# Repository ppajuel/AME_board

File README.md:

# AME_board
AME_board (Aquila Mobile Expansio board) is a low cost expansion board for IGEP COM AQUILA. This board allows to use [IGEP COM AQUILA AM335x](https://isee.biz/products/igep-processor-boards/igep-com-aquila-am335x) as a battery powered M2M device. Its features are:

* Lipo Bat handler and 5V step-UP
* Modem GPRS with ANT conn
* Serial debug 3v3
* Jumper boot
* RTC BAT
* Switch POWERKILL
* PCB frendly and soldable
* MicroUSB power
* Optional: debug all SODIMM
* Bat connector and Header

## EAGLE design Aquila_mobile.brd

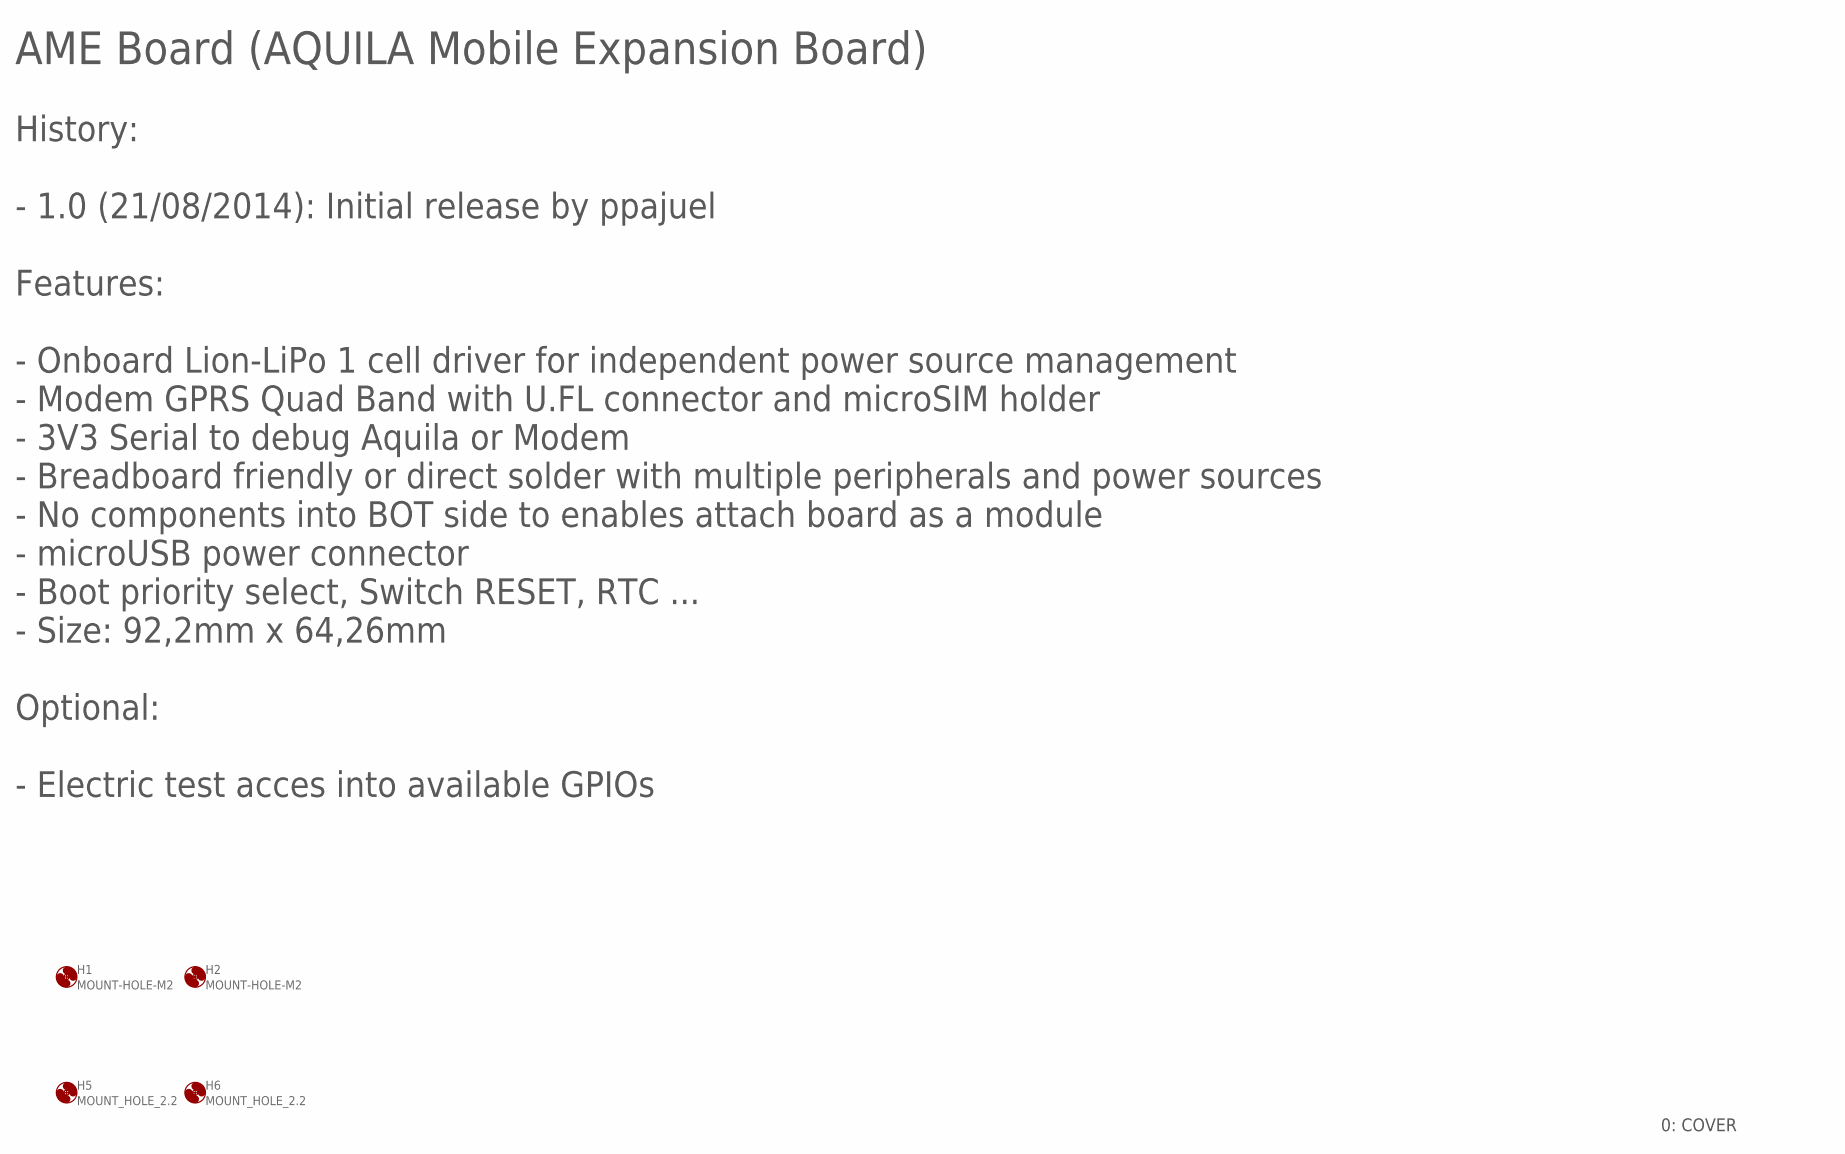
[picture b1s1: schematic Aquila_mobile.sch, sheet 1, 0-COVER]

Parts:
H1, H2: MOUNT-HOLE-M2; 5,0
H5, H6: MOUNT_HOLE_2.2; HOLE-2.2

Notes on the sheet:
History: - 1.0 (21/08/2014): Initial release by ppajuel Features: - Onboard Lion-LiPo 1 cell driver for independent power source management - Modem GPRS Quad Band with U.FL connector and microSIM holder - 3V3 Serial to debug Aquila or Modem - Breadboard friendly or direct solder with multiple perip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
AME Board (AQUILA Mobile Expansion Board)
0: COVER

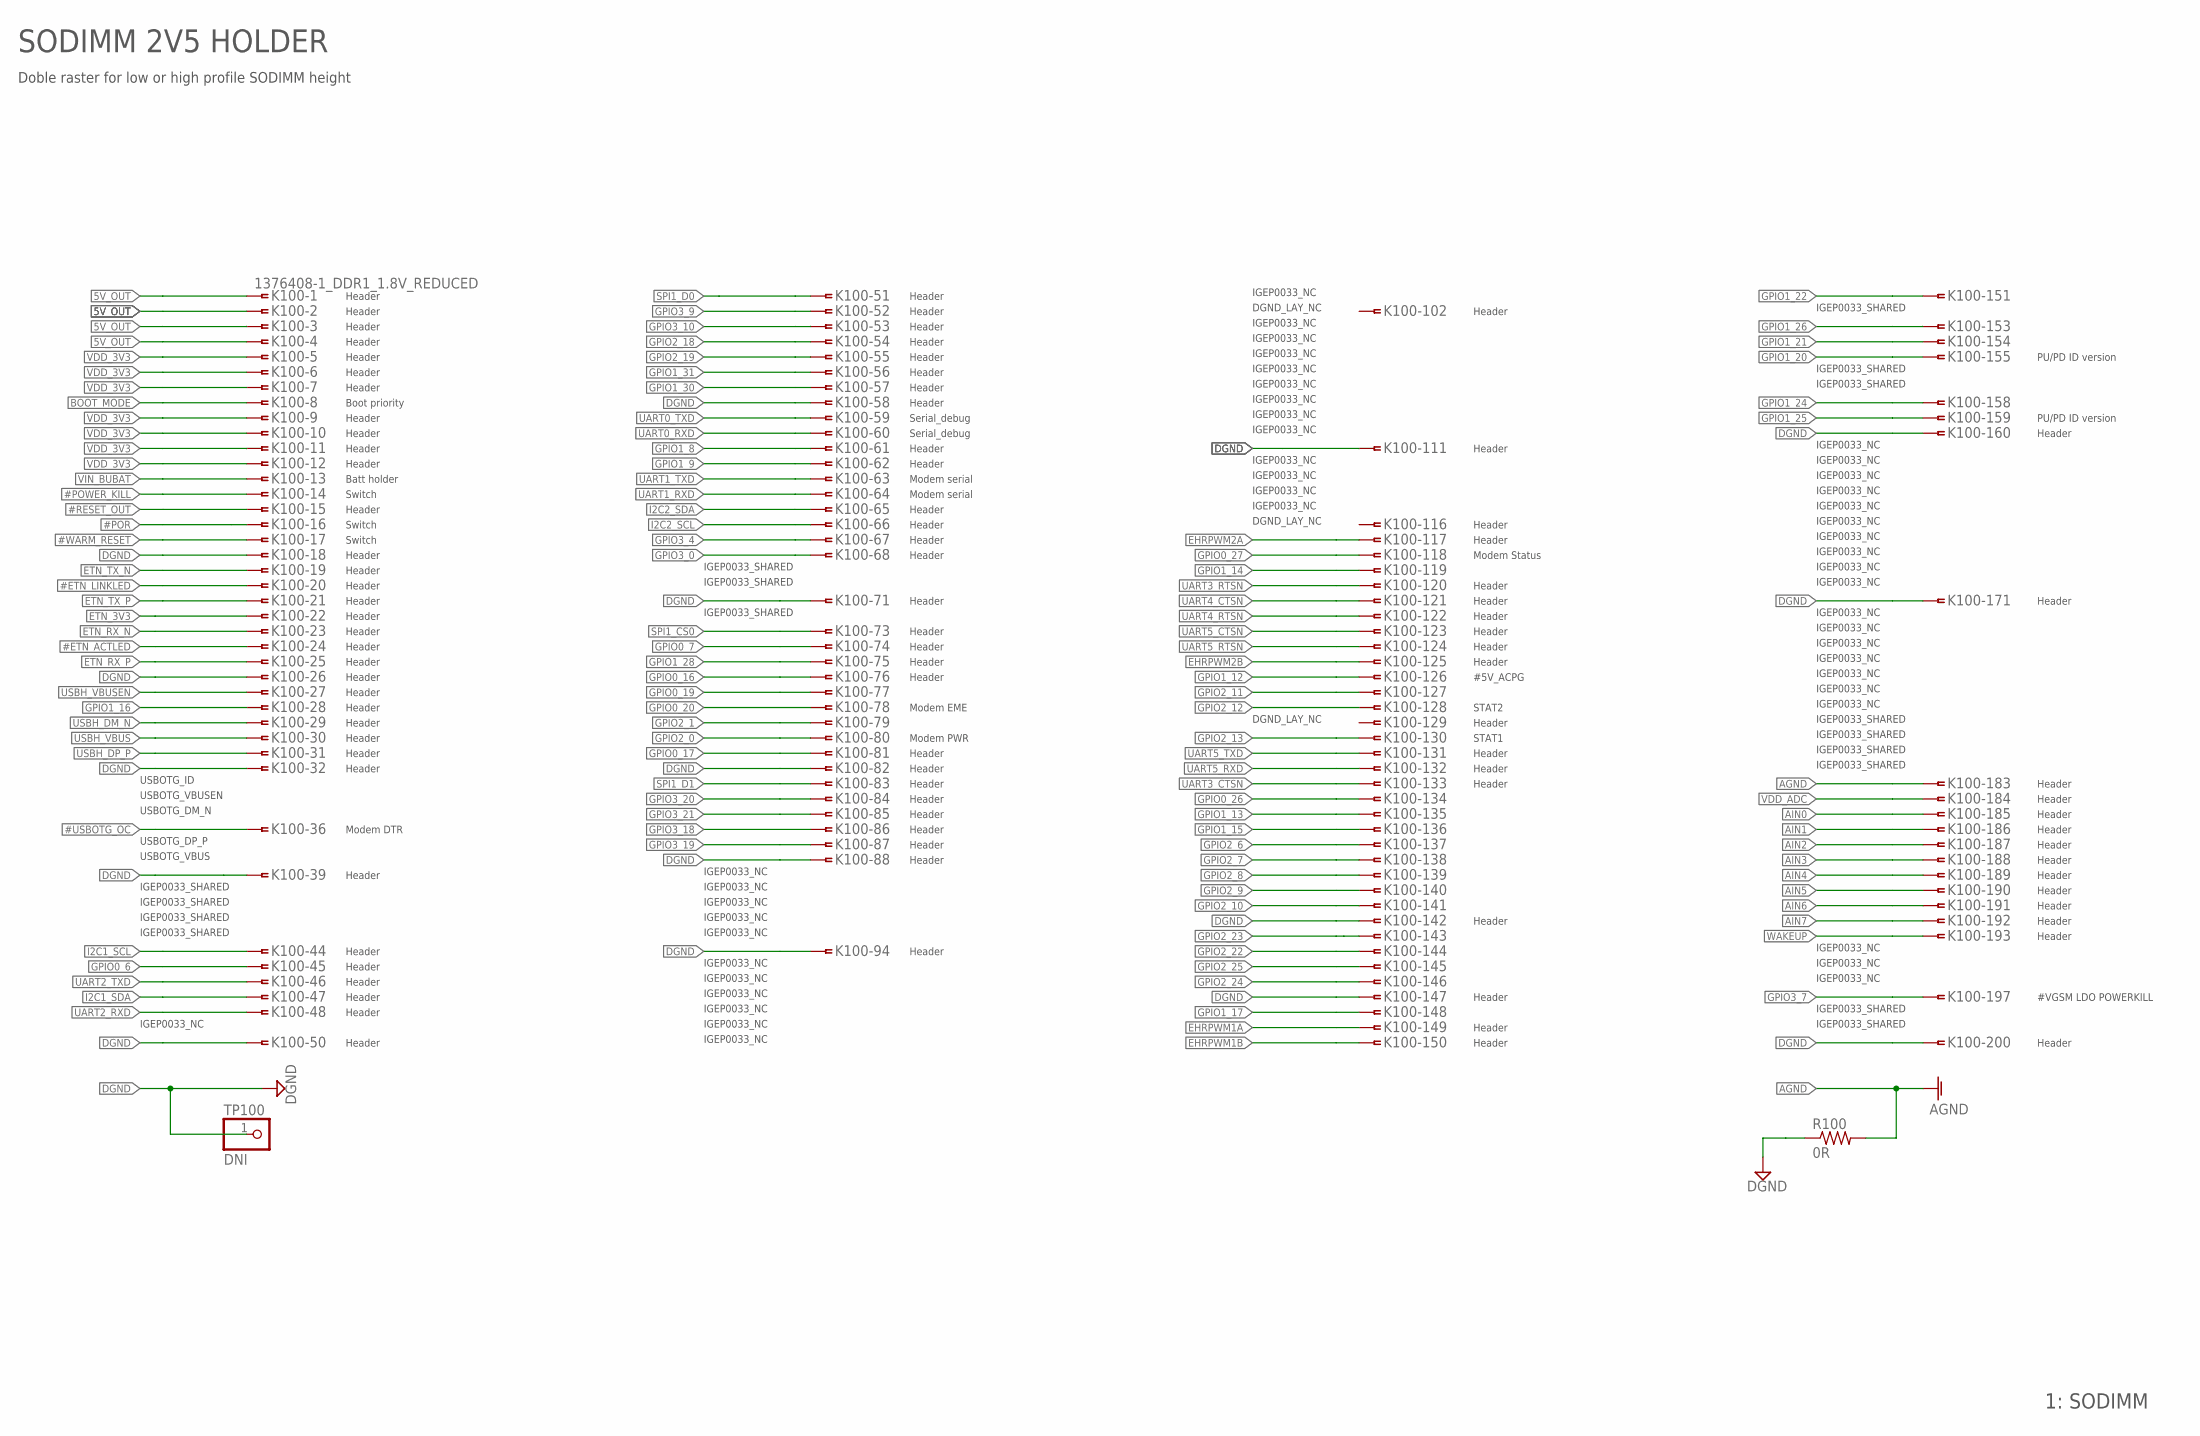
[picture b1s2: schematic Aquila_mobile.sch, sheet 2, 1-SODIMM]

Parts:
K100: 1376408-1_DDR1_1.8V_REDUCED; 1-1376408-1_REDUCED
R100: 0R; R0402
TP100: DNI; 1X01

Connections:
5V_OUT: K100.1, K100.2, K100.3, K100.4; also elsewhere on the board
#ETN_ACTLED: K100.24; also elsewhere on the board
#ETN_LINKLED: K100.20; also elsewhere on the board
#POR: K100.16; also elsewhere on the board
#POWER_KILL: K100.14; also elsewhere on the board
#RESET_OUT: K100.15; also elsewhere on the board
#USBOTG_OC: K100.36; also elsewhere on the board
#WARM_RESET: K100.17; also elsewhere on the board
AGND: K100.183, R100.2; also elsewhere on the board
AIN0: K100.185; also elsewhere on the board
AIN1: K100.186; also elsewhere on the board
AIN2: K100.187; also elsewhere on the board
AIN3: K100.188; also elsewhere on the board
AIN4: K100.189; also elsewhere on the board
AIN5: K100.190; also elsewhere on the board
AIN6: K100.191; also elsewhere on the board
AIN7: K100.192; also elsewhere on the board
BOOT_MODE: K100.8; also elsewhere on the board
DGND: K100.18, K100.26, K100.32, K100.39, K100.50, K100.58, K100.71, K100.82, K100.88, K100.94, K100.111, K100.142, K100.147, K100.160, K100.171, K100.200, R100.1, TP100.1; also elsewhere on the board
EHRPWM1A: K100.149; also elsewhere on the board
EHRPWM1B: K100.150; also elsewhere on the board
EHRPWM2A: K100.117; also elsewhere on the board
EHRPWM2B: K100.125; also elsewhere on the board
ETN_3V3: K100.22; also elsewhere on the board
ETN_RX_N: K100.23; also elsewhere on the board
ETN_RX_P: K100.25; also elsewhere on the board
ETN_TX_N: K100.19; also elsewhere on the board
ETN_TX_P: K100.21; also elsewhere on the board
GPIO0_6: K100.45; also elsewhere on the board
GPIO0_7: K100.74; also elsewhere on the board
GPIO0_16: K100.76; also elsewhere on the board
GPIO0_17: K100.81; also elsewhere on the board
GPIO0_19: K100.77; also elsewhere on the board
GPIO0_20: K100.78; also elsewhere on the board
GPIO0_26: K100.134; also elsewhere on the board
GPIO0_27: K100.118; also elsewhere on the board
GPIO1_8: K100.61; also elsewhere on the board
GPIO1_9: K100.62; also elsewhere on the board
GPIO1_12: K100.126; also elsewhere on the board
GPIO1_13: K100.135; also elsewhere on the board
GPIO1_14: K100.119; also elsewhere on the board
GPIO1_15: K100.136; also elsewhere on the board
GPIO1_16: K100.28; also elsewhere on the board
GPIO1_17: K100.148; also elsewhere on the board
GPIO1_20: K100.155; also elsewhere on the board
GPIO1_21: K100.154; also elsewhere on the board
GPIO1_22: K100.151; also elsewhere on the board
GPIO1_24: K100.158; also elsewhere on the board
GPIO1_25: K100.159; also elsewhere on the board
GPIO1_26: K100.153; also elsewhere on the board
GPIO1_28: K100.75; also elsewhere on the board
GPIO1_30: K100.57; also elsewhere on the board
GPIO1_31: K100.56; also elsewhere on the board
GPIO2_0: K100.80; also elsewhere on the board
GPIO2_1: K100.79; also elsewhere on the board
GPIO2_6: K100.137; also elsewhere on the board
GPIO2_7: K100.138; also elsewhere on the board
GPIO2_8: K100.139; also elsewhere on the board
GPIO2_9: K100.140; also elsewhere on the board
GPIO2_10: K100.141; also elsewhere on the board
GPIO2_11: K100.127; also elsewhere on the board
GPIO2_12: K100.128; also elsewhere on the board
GPIO2_13: K100.130; also elsewhere on the board
GPIO2_18: K100.54; also elsewhere on the board
GPIO2_19: K100.55; also elsewhere on the board
GPIO2_22: K100.144; also elsewhere on the board
GPIO2_23: K100.143; also elsewhere on the board
GPIO2_24: K100.146; also elsewhere on the board
GPIO2_25: K100.145; also elsewhere on the board
GPIO3_0: K100.68; also elsewhere on the board
GPIO3_4: K100.67; also elsewhere on the board
GPIO3_7: K100.197; also elsewhere on the board
GPIO3_9: K100.52; also elsewhere on the board
GPIO3_10: K100.53; also elsewhere on the board
GPIO3_18: K100.86; also elsewhere on the board
GPIO3_19: K100.87; also elsewhere on the board
GPIO3_20: K100.84; also elsewhere on the board
GPIO3_21: K100.85; also elsewhere on the board
I2C1_SCL: K100.44; also elsewhere on the board
I2C1_SDA: K100.47; also elsewhere on the board
I2C2_SCL: K100.66; also elsewhere on the board
I2C2_SDA: K100.65; also elsewhere on the board
SPI1_CS0: K100.73; also elsewhere on the board
SPI1_D0: K100.51; also elsewhere on the board
SPI1_D1: K100.83; also elsewhere on the board
UART0_RXD: K100.60; also elsewhere on the board
UART0_TXD: K100.59; also elsewhere on the board
UART1_RXD: K100.64; also elsewhere on the board
UART1_TXD: K100.63; also elsewhere on the board
UART2_RXD: K100.48; also elsewhere on the board
UART2_TXD: K100.46; also elsewhere on the board
UART3_CTSN: K100.133; also elsewhere on the board
UART3_RTSN: K100.120; also elsewhere on the board
UART4_CTSN: K100.121; also elsewhere on the board
UART4_RTSN: K100.122; also elsewhere on the board
UART5_CTSN: K100.123; also elsewhere on the board
UART5_RTSN: K100.124; also elsewhere on the board
UART5_RXD: K100.132; also elsewhere on the board
UART5_TXD: K100.131; also elsewhere on the board
USBH_DM_N: K100.29; also elsewhere on the board
USBH_DP_P: K100.31; also elsewhere on the board
USBH_VBUS: K100.30; also elsewhere on the board
USBH_VBUSEN: K100.27; also elsewhere on the board
VDD_3V3: K100.5, K100.6, K100.7, K100.9, K100.10, K100.11, K100.12; also elsewhere on the board
VDD_ADC: K100.184; also elsewhere on the board
VIN_BUBAT: K100.13; also elsewhere on the board
WAKEUP: K100.193; also elsewhere on the board

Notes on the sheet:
SODIMM 2V5 HOLDER
USBOTG_ID
USBOTG_VBUSEN
USBOTG_DM_N
USBOTG_DP_P
USBOTG_VBUS
IGEP0033_SHARED
IGEP0033_NC
Serial_debug
Switch
Boot priority
Modem serial
Modem EME
#VGSM LDO POWERKILL
#5V_ACPG
STAT1
STAT2
1: SODIMM
Doble raster for low or high profile SODIMM height
Batt holder
Modem DTR
Modem PWR
Header
PU/PD ID version
Modem Status
DGND_LAY_NC

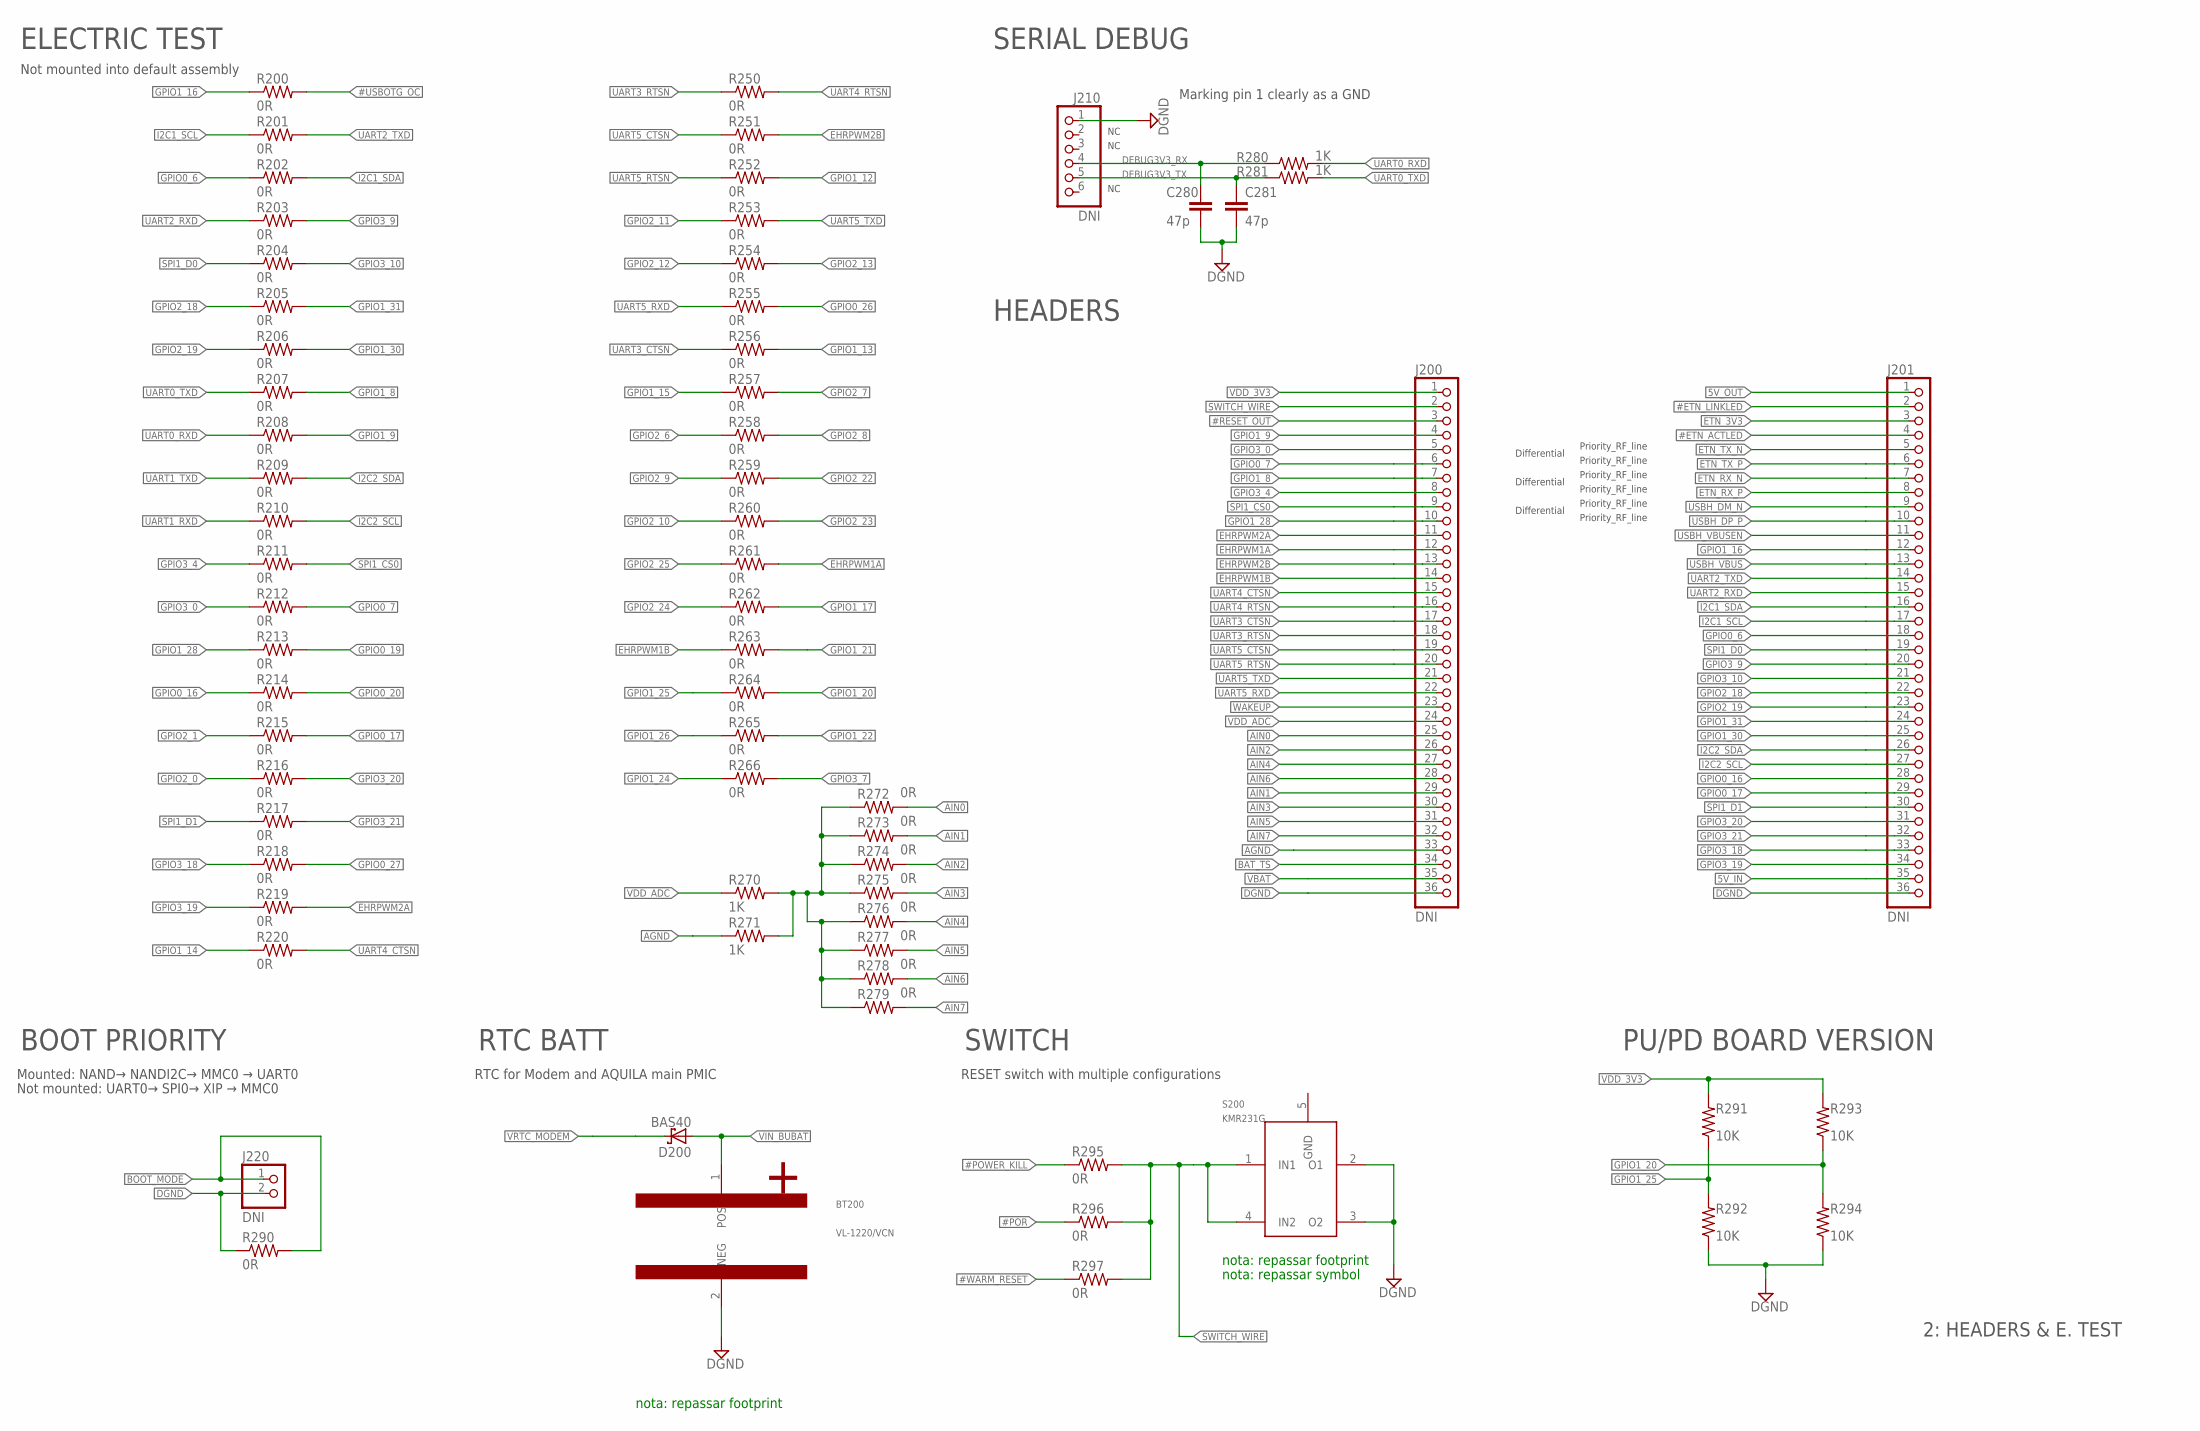
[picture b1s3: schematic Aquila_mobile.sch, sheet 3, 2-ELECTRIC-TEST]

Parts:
BT200: VL-1220/VCN
C280, C281: 47p; C0603
D200: BAS40; SOT23
J200, J201: DNI; 1X36
J210: DNI; 1X06
J220: DNI; 1X02
R200, R201, R202, R203, R204, R205, R206, R207, R208, R209, R210, R211, R212, R213, R214, R215, R216, R217, R218, R219, R220, R250, R251, R252, R253, R254, R255, R256, R257, R258, R259, R260, R262, R263, R264, R265, R266, R272, R273, R274, R275, R276, R277, R278, R279, R295, R296, R297: 0R; R0201
R261, R290: 0R; R0402
R270, R271: 1K; R0402
R280, R281: 1K; R0603
R291, R292, R293, R294: 10K; R0402
S200: KMR231G

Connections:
5V_IN: J201.35; also elsewhere on the board
5V_OUT: J201.1; also elsewhere on the board
#ETN_ACTLED: J201.4; also elsewhere on the board
#ETN_LINKLED: J201.2; also elsewhere on the board
#POR: R296.1; also elsewhere on the board
#POWER_KILL: R295.1; also elsewhere on the board
#RESET_OUT: J200.3; also elsewhere on the board
#USBOTG_OC: R200.2; also elsewhere on the board
#WARM_RESET: R297.1; also elsewhere on the board
ADCREFERENCE: R270.2, R271.2, R272.1, R273.1, R274.1, R275.1, R276.1, R277.1, R278.1, R279.1
AGND: J200.33, R271.1; also elsewhere on the board
AIN0: J200.25, R272.2; also elsewhere on the board
AIN1: J200.29, R273.2; also elsewhere on the board
AIN2: J200.26, R274.2; also elsewhere on the board
AIN3: J200.30, R275.2; also elsewhere on the board
AIN4: J200.27, R276.2; also elsewhere on the board
AIN5: J200.31, R277.2; also elsewhere on the board
AIN6: J200.28, R278.2; also elsewhere on the board
AIN7: J200.32, R279.2; also elsewhere on the board
BAT_TS: J200.34; also elsewhere on the board
BOOT_MODE: J220.1, R290.2; also elsewhere on the board
DEBUG3V3_RX: C280.1, J210.4, R280.1; also elsewhere on the board
DEBUG3V3_TX: C281.1, J210.5, R281.1; also elsewhere on the board
DGND: BT200.2 (NEG), C280.2, C281.2, J200.36, J201.36, J210.1, J220.2, R290.1, R292.1, R294.1, S200.2 (O1), S200.3 (O2); also elsewhere on the board
EHRPWM1A: J200.12, R261.2; also elsewhere on the board
EHRPWM1B: J200.14, R263.1; also elsewhere on the board
EHRPWM2A: J200.11, R219.2; also elsewhere on the board
EHRPWM2B: J200.13, R251.2; also elsewhere on the board
ETN_3V3: J201.3; also elsewhere on the board
ETN_RX_N: J201.7; also elsewhere on the board
ETN_RX_P: J201.8; also elsewhere on the board
ETN_TX_N: J201.5; also elsewhere on the board
ETN_TX_P: J201.6; also elsewhere on the board
GPIO0_6: J201.18, R202.1; also elsewhere on the board
GPIO0_7: J200.6, R212.2; also elsewhere on the board
GPIO0_16: J201.28, R214.1; also elsewhere on the board
GPIO0_17: J201.29, R215.2; also elsewhere on the board
GPIO0_19: R213.2; also elsewhere on the board
GPIO0_20: R214.2; also elsewhere on the board
GPIO0_26: R255.2; also elsewhere on the board
GPIO0_27: R218.2; also elsewhere on the board
GPIO1_8: J200.7, R207.2; also elsewhere on the board
GPIO1_9: J200.4, R208.2; also elsewhere on the board
GPIO1_12: R252.2; also elsewhere on the board
GPIO1_13: R256.2; also elsewhere on the board
GPIO1_14: R220.1; also elsewhere on the board
GPIO1_15: R257.1; also elsewhere on the board
GPIO1_16: J201.12, R200.1; also elsewhere on the board
GPIO1_17: R262.2; also elsewhere on the board
GPIO1_20: R264.2, R293.1, R294.2; also elsewhere on the board
GPIO1_21: R263.2; also elsewhere on the board
GPIO1_22: R265.2; also elsewhere on the board
GPIO1_24: R266.1; also elsewhere on the board
GPIO1_25: R264.1, R291.1, R292.2; also elsewhere on the board
GPIO1_26: R265.1; also elsewhere on the board
GPIO1_28: J200.10, R213.1; also elsewhere on the board
GPIO1_30: J201.25, R206.2; also elsewhere on the board
GPIO1_31: J201.24, R205.2; also elsewhere on the board
GPIO2_0: R216.1; also elsewhere on the board
GPIO2_1: R215.1; also elsewhere on the board
GPIO2_6: R258.1; also elsewhere on the board
GPIO2_7: R257.2; also elsewhere on the board
GPIO2_8: R258.2; also elsewhere on the board
GPIO2_9: R259.1; also elsewhere on the board
GPIO2_10: R260.1; also elsewhere on the board
GPIO2_11: R253.1; also elsewhere on the board
GPIO2_12: R254.1; also elsewhere on the board
GPIO2_13: R254.2; also elsewhere on the board
GPIO2_18: J201.22, R205.1; also elsewhere on the board
GPIO2_19: J201.23, R206.1; also elsewhere on the board
GPIO2_22: R259.2; also elsewhere on the board
GPIO2_23: R260.2; also elsewhere on the board
GPIO2_24: R262.1; also elsewhere on the board
GPIO2_25: R261.1; also elsewhere on the board
GPIO3_0: J200.5, R212.1; also elsewhere on the board
GPIO3_4: J200.8, R211.1; also elsewhere on the board
GPIO3_7: R266.2; also elsewhere on the board
GPIO3_9: J201.20, R203.2; also elsewhere on the board
GPIO3_10: J201.21, R204.2; also elsewhere on the board
GPIO3_18: J201.33, R218.1; also elsewhere on the board
GPIO3_19: J201.34, R219.1; also elsewhere on the board
GPIO3_20: J201.31, R216.2; also elsewhere on the board
GPIO3_21: J201.32, R217.2; also elsewhere on the board
I2C1_SCL: J201.17, R201.1; also elsewhere on the board
I2C1_SDA: J201.16, R202.2; also elsewhere on the board
I2C2_SCL: J201.27, R210.2; also elsewhere on the board
I2C2_SDA: J201.26, R209.2; also elsewhere on the board
SPI1_CS0: J200.9, R211.2; also elsewhere on the board
SPI1_D0: J201.19, R204.1; also elsewhere on the board
SPI1_D1: J201.30, R217.1; also elsewhere on the board
SWITCH_WIRE: J200.2, R295.2, R296.2, R297.2, S200.1 (IN1), S200.4 (IN2)
UART0_RXD: R208.1, R280.2; also elsewhere on the board
UART0_TXD: R207.1, R281.2; also elsewhere on the board
UART1_RXD: R210.1; also elsewhere on the board
UART1_TXD: R209.1; also elsewhere on the board
UART2_RXD: J201.15, R203.1; also elsewhere on the board
UART2_TXD: J201.14, R201.2; also elsewhere on the board
UART3_CTSN: J200.17, R256.1; also elsewhere on the board
UART3_RTSN: J200.18, R250.1; also elsewhere on the board
UART4_CTSN: J200.15, R220.2; also elsewhere on the board
UART4_RTSN: J200.16, R250.2; also elsewhere on the board
UART5_CTSN: J200.19, R251.1; also elsewhere on the board
UART5_RTSN: J200.20, R252.1; also elsewhere on the board
UART5_RXD: J200.22, R255.1; also elsewhere on the board
UART5_TXD: J200.21, R253.2; also elsewhere on the board
USBH_DM_N: J201.9; also elsewhere on the board
USBH_DP_P: J201.10; also elsewhere on the board
USBH_VBUS: J201.13; also elsewhere on the board
USBH_VBUSEN: J201.11; also elsewhere on the board
VBAT: J200.35; also elsewhere on the board
VDD_3V3: J200.1, R291.2, R293.2; also elsewhere on the board
VDD_ADC: J200.24, R270.1; also elsewhere on the board
VIN_BUBAT: BT200.1 (POS), D200.1 (A); also elsewhere on the board
VRTC_MODEM: D200.3 (C); also elsewhere on the board
WAKEUP: J200.23; also elsewhere on the board

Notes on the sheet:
ELECTRIC TEST
BOOT PRIORITY
RTC BATT
SWITCH
nota: repassar footprint
SERIAL DEBUG
HEADERS
Marking pin 1 clearly as a GND
Not mounted into default assembly
Mounted: NAND→ NANDI2C→ MMC0 → UART0
Not mounted: UART0→ SPI0→ XIP → MMC0
nota: repassar symbol
2: HEADERS & E. TEST
RTC for Modem and AQUILA main PMIC
RESET switch with multiple configurations
Priority_RF_line
Differential
PU/PD BOARD VERSION

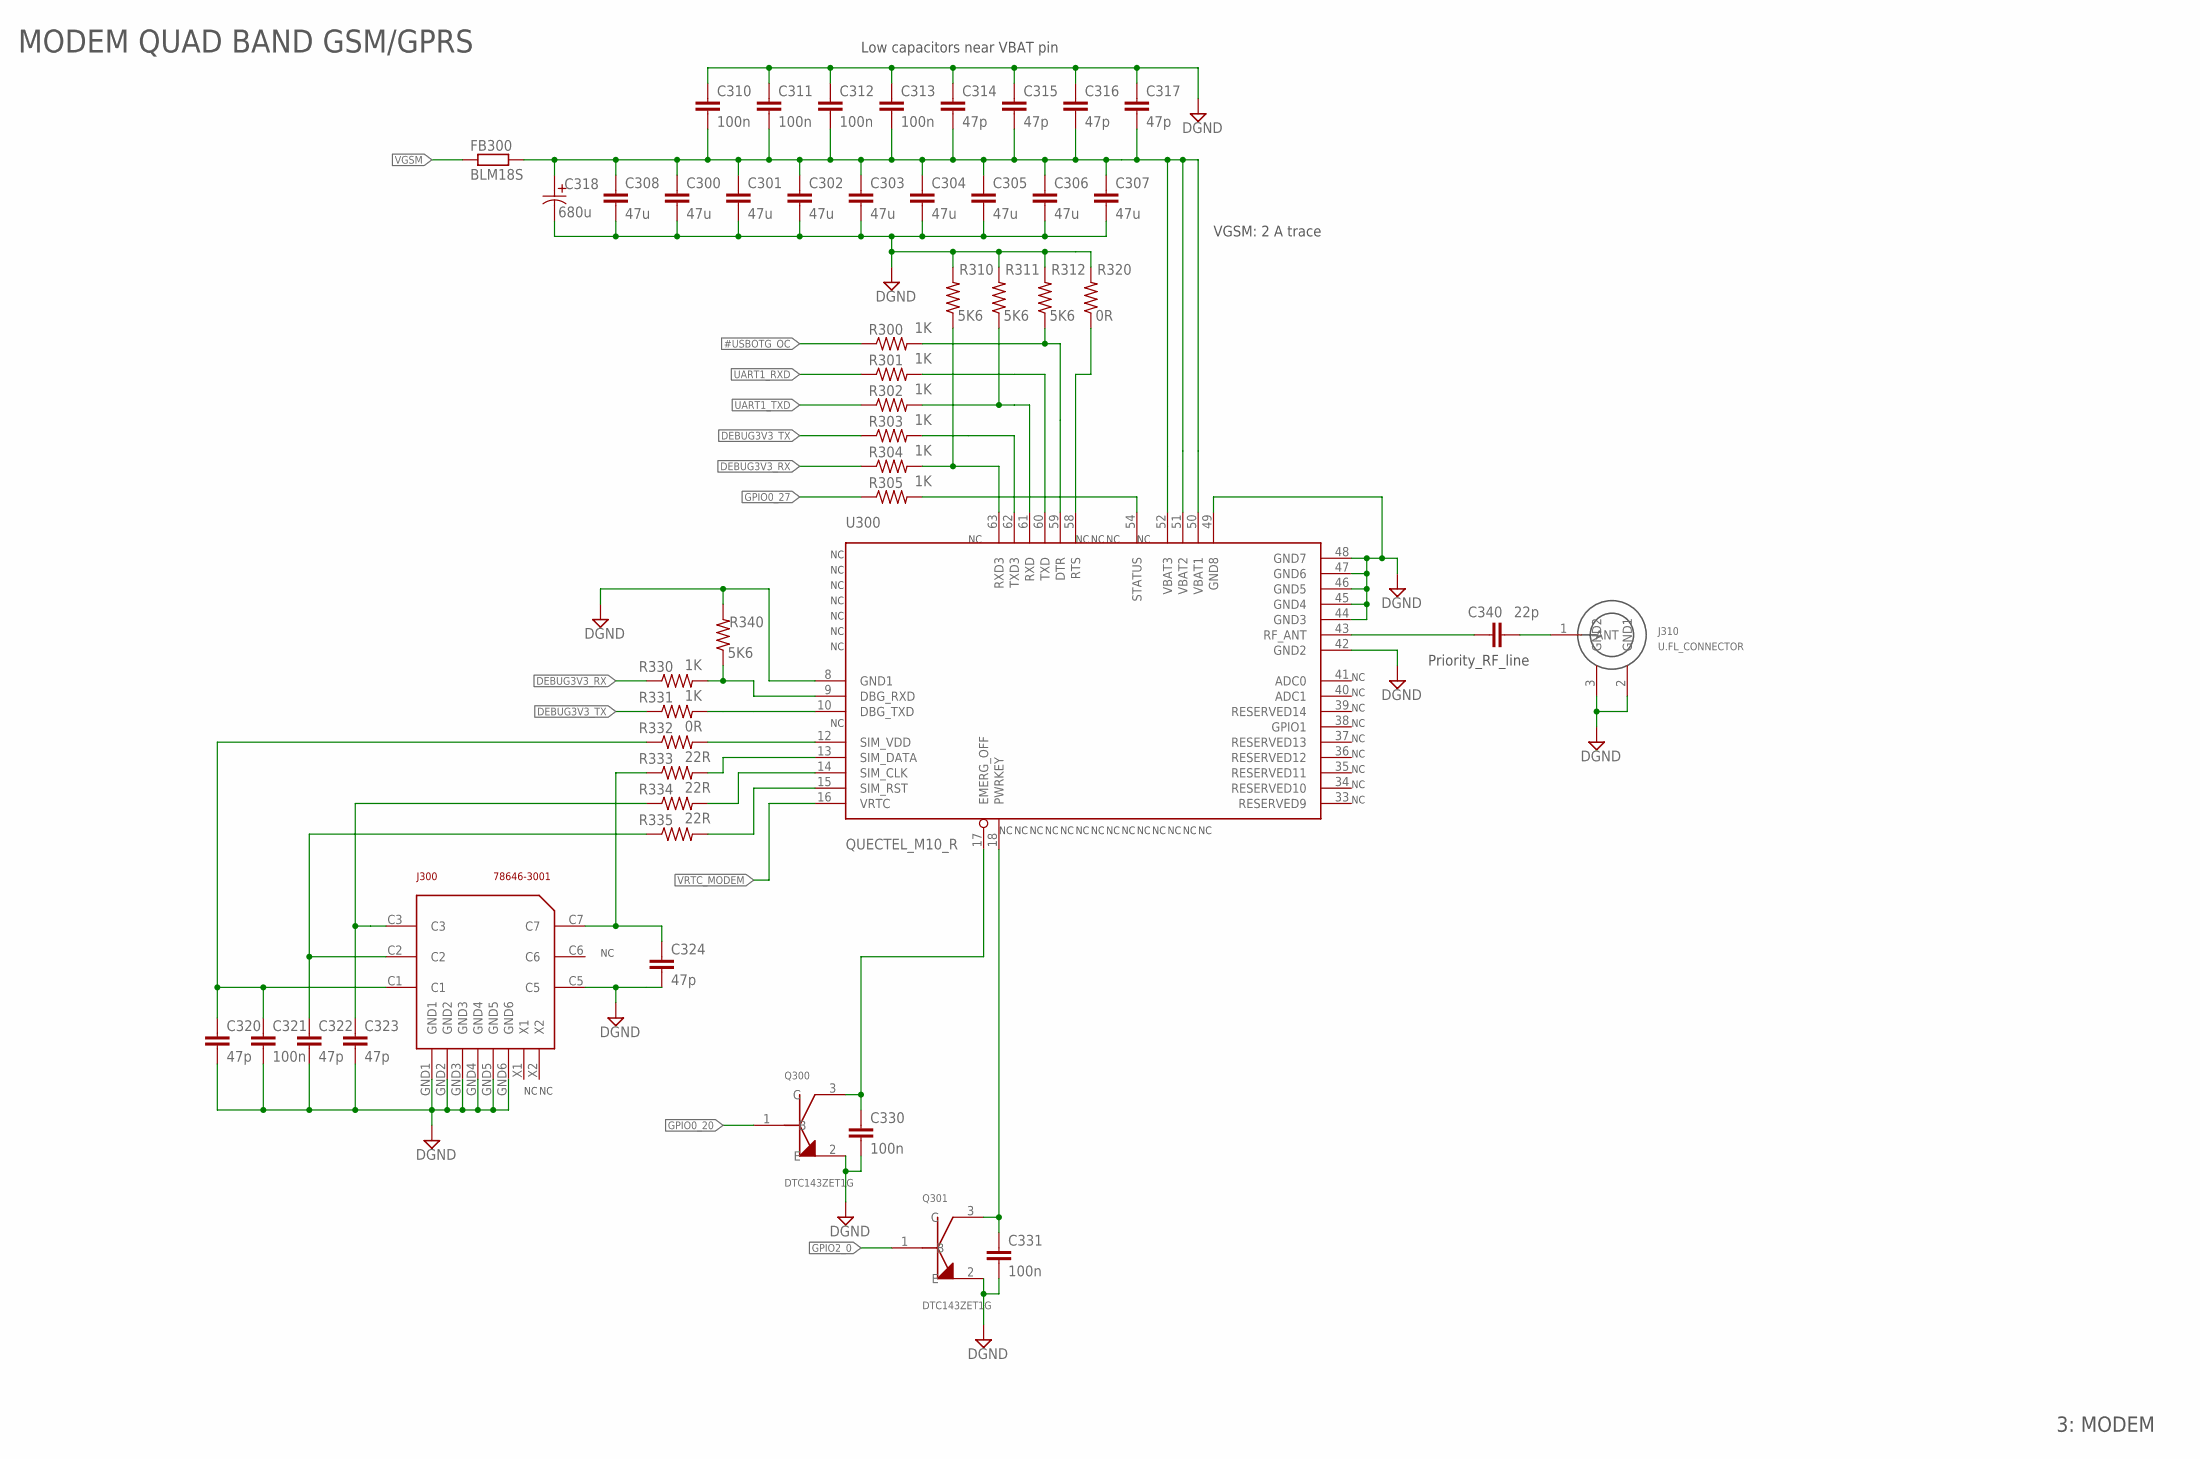
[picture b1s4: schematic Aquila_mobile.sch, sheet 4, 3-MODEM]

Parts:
C300, C301, C302, C303, C304, C305, C306, C307, C308: 47u; C0805
C310, C311, C312, C313, C321, C330, C331: 100n; C0603
C314, C315, C316, C317, C320, C322, C323, C324: 47p; C0603
C318: 680u; CAPAE660X800N
C340: 22p; C0402K
FB300: BLM18S; R0603
J300: 78646-3001
J310: U.FL_CONNECTOR; U.FL_RECEPTACLE
Q300, Q301: DTC143ZET1G; SOT-416
R300, R301, R302, R303, R304, R305, R330, R331: 1K; R0603
R310, R311, R312, R340: 5K6; R0603
R320, R332: 0R; R0603
R333, R334, R335: 22R; R0603
U300: QUECTEL_M10_R; QUECTEL_M10

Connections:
#USBOTG_OC: R300.1; also elsewhere on the board
C400: C340.1, U300.43 (RF_ANT)
DEBUG3V3_RX: R304.1, R330.1; also elsewhere on the board
DEBUG3V3_TX: R303.1, R331.1; also elsewhere on the board
DGND: C300.2, C301.2, C302.2, C303.2, C304.2, C305.2, C306.2, C307.2, C308.2, C310.1, C311.1, C312.1, C313.1, C314.1, C315.1, C316.1, C317.1, C318.2, C320.2, C321.2, C322.2, C323.2, C324.2, C330.2, C331.2, J300.C5, J300.GND1, J300.GND2, J300.GND3, J300.GND4, J300.GND5, J300.GND6, J310.2 (GND1), J310.3 (GND2), Q300.2 (E), Q301.2 (E), R310.2, R311.2, R312.2, R320.2, R340.2, U300.8 (GND1), U300.42 (GND2), U300.44 (GND3), U300.45 (GND4), U300.46 (GND5), U300.47 (GND6), U300.48 (GND7), U300.49 (GND8); also elsewhere on the board
GPIO0_20: Q300.1 (B); also elsewhere on the board
GPIO0_27: R305.1; also elsewhere on the board
GPIO2_0: Q301.1 (B); also elsewhere on the board
unnamed: R305.2, U300.54 (STATUS)
unnamed: C340.2, J310.1 (ANT)
unnamed: C300.1, C301.1, C302.1, C303.1, C304.1, C305.1, C306.1, C307.1, C308.1, C310.2, C311.2, C312.2, C313.2, C314.2, C315.2, C316.2, C317.2, C318.1, FB300.2, U300.50 (VBAT1), U300.51 (VBAT2), U300.52 (VBAT3)
unnamed: R301.2, U300.60 (TXD)
unnamed: R302.2, R311.1, U300.61 (RXD)
unnamed: R303.2, U300.62 (TXD3)
unnamed: R320.1, U300.58 (RTS)
unnamed: R304.2, R310.1, U300.63 (RXD3)
unnamed: R332.2, U300.12 (SIM_VDD)
unnamed: R333.2, U300.13 (SIM_DATA)
unnamed: R330.2, R340.1, U300.9 (DBG_RXD)
unnamed: R331.2, U300.10 (DBG_TXD)
unnamed: R334.2, U300.14 (SIM_CLK)
unnamed: R335.2, U300.15 (SIM_RST)
unnamed: C320.1, C321.1, J300.C1, R332.1
unnamed: C324.1, J300.C7, R333.1
unnamed: C330.1, Q300.3 (C), U300.17 (EMERG_OFF)
unnamed: C322.1, J300.C2, R335.1
unnamed: C323.1, J300.C3, R334.1
unnamed: C331.1, Q301.3 (C), U300.18 (PWRKEY)
unnamed: R300.2, R312.1, U300.59 (DTR)
UART1_RXD: R301.1; also elsewhere on the board
UART1_TXD: R302.1; also elsewhere on the board
VGSM: FB300.1; also elsewhere on the board
VRTC_MODEM: U300.16 (VRTC); also elsewhere on the board

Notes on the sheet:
MODEM QUAD BAND GSM/GPRS
Low capacitors near VBAT pin
VGSM: 2 A trace
3: MODEM
Priority_RF_line
